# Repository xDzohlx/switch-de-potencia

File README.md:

# switch-de-potencia
Switch de alta corriente para encender baterías para suministrar potencia para un robot de combate para 180 amp 35V

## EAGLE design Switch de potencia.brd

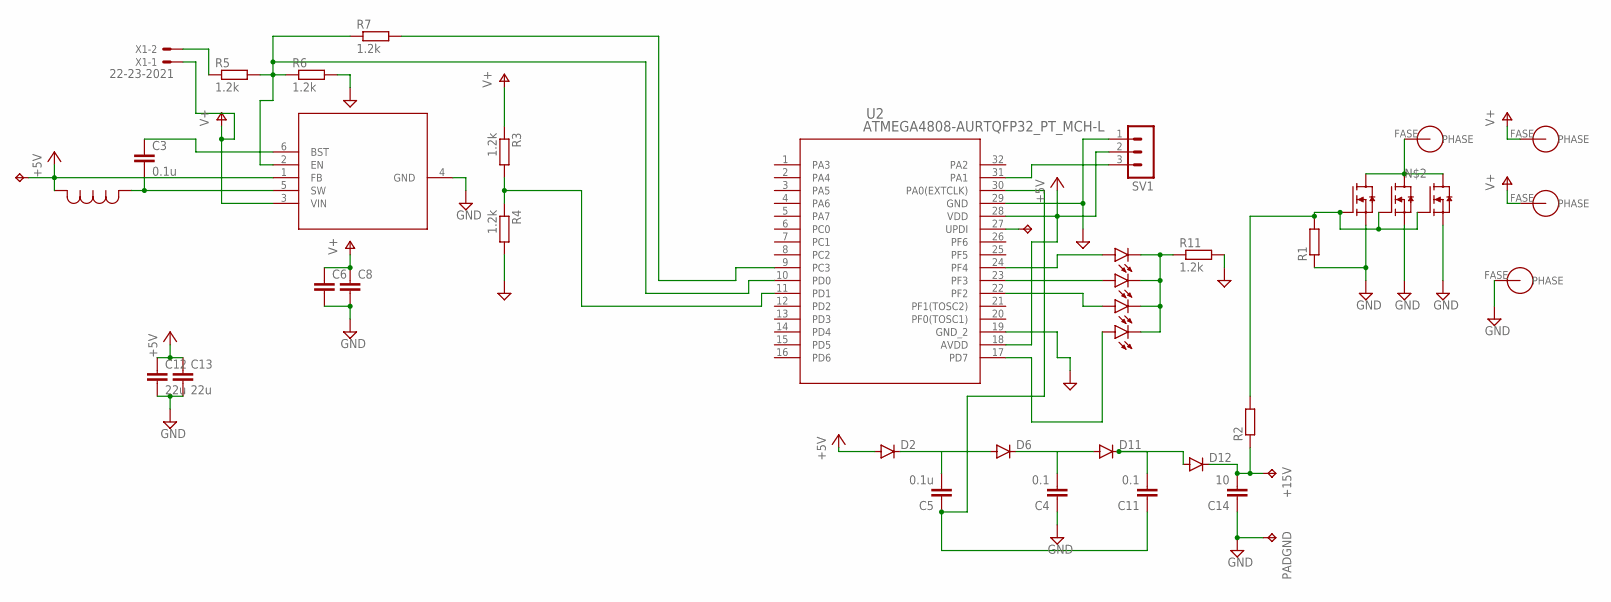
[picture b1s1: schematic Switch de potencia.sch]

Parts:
+15V: TPB1,27; B1,27
C3: 0.1u; C0402
C4, C11: 0.1; C0805
C5: 0.1u; C0805
C6, C8: C-EUC0805; C0805
C12, C13: 22u; C0402
C14: 10; C0805
D2, D6, D11, D12: DIODE-MINIMELF; MINIMELF
GND: PHASE; POWEROUT
LA1, LA2, LA3: IPB180N06S4-H1; PG-TO263-7-3
OUTPUT: PHASE; POWEROUT
PADGND: TPB1,27; B1,27
POWERON2, POWERON3, POWERON4, POWERON5: LEDCHIPLED_0603; CHIPLED_0603
R1, R2: R-EU_R0603; R0603
R3, R4, R5, R6, R7, R11: 1.2k; M0805
SV1: MA03-1
TP1, TP9: TPB1,27; B1,27
U2: ATMEGA4808-AURTQFP32_PT_MCH-L; TQFP32_PT_MCH-L
U3: AP63205WU-7SOIC_05WU-7_DIO-M; SOIC_05WU-7_DIO-M
U$1: INDUCTOR4.7; IND_NRS5030T100MMGJ_TAY
V+, V+1: PHASE; POWEROUT
X1: 22-23-2021

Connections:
+5V: C12.1, C13.1, D2.A, SV1.2, TP9.TP, U2.18 (AVDD), U2.28 (VDD), U3.1 (FB), U$1.1
GND: C4.1, C6.2, C8.2, C12.2, C13.2, C14.1, GND.FASE, LA1.2 (S), LA1.3 (S), LA1.5 (S), LA1.6 (S), LA1.7 (S), LA2.2 (S), LA2.3 (S), LA2.5 (S), LA2.6 (S), LA2.7 (S), LA3.2 (S), LA3.3 (S), LA3.5 (S), LA3.6 (S), LA3.7 (S), PADGND.TP, R1.1, R4.2, R6.2, R11.2, SV1.1, U2.19 (GND_2), U2.29 (GND), U3.4 (GND)
unnamed: LA1.1 (G), LA2.1 (G), LA3.1 (G), R1.2, R2.2
unnamed: LA1.8 (D), LA2.8 (D), LA3.8 (D), OUTPUT.FASE
unnamed: TP1.TP, U2.27 (UPDI)
unnamed: POWERON3.A, U2.24 (PF4)
unnamed: POWERON2.A, U2.23 (PF3)
unnamed: POWERON5.A, U2.22 (PF2)
unnamed: +15V.TP, C14.2, D12.C, R2.1
unnamed: C5.2, D2.C, D6.A
unnamed: R5.1, X1.2
unnamed: R3.2, R4.1, U2.11 (PD1)
unnamed: POWERON4.A, U2.17 (PD7)
unnamed: SV1.3, U2.31 (PA1)
unnamed: POWERON2.C, POWERON3.C, POWERON4.C, POWERON5.C, R11.1
unnamed: C3.2, U3.5 (SW), U$1.2
unnamed: R5.2, R6.1, R7.1, U2.10 (PD0), U3.2 (EN)
unnamed: R7.2, U2.9 (PC3)
unnamed: C5.1, C11.1, U2.30 (PA0(EXTCLK))
unnamed: C3.1, U3.6 (BST)
unnamed: C4.2, D6.C, D11.A
unnamed: C11.2, D11.C, D12.A
V+: C6.1, C8.1, R3.1, U3.3 (VIN), V+.FASE, V+1.FASE, X1.1

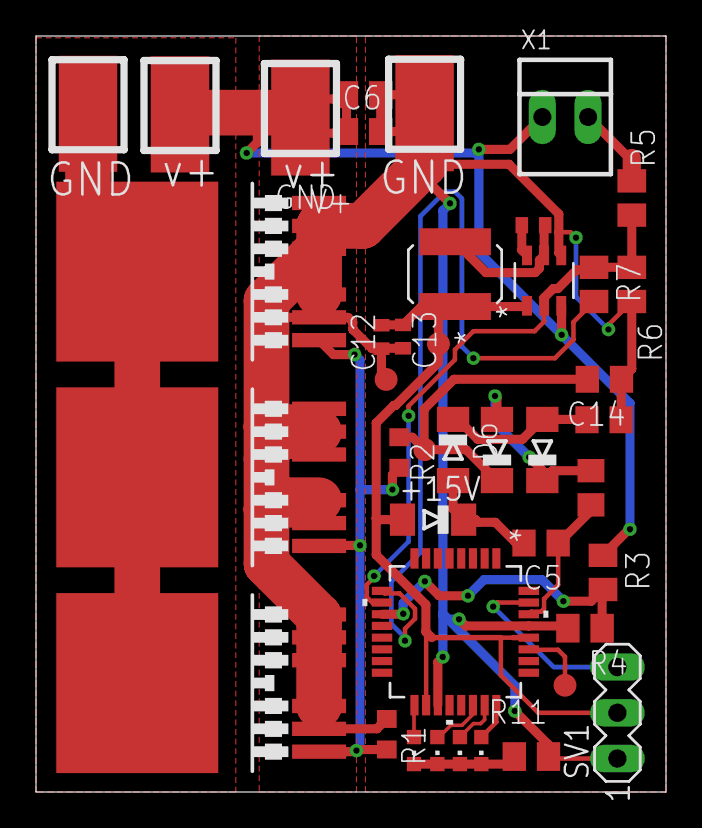
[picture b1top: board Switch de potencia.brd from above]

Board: 2 copper layers, 35.0 x 42.0 mm, 41 parts (0 on the bottom side), 23 nets.

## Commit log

2021-02-15 Add files via upload
    v1
2021-02-17 Create pcb
2021-02-21 Add files via upload
    Agregue usart , un pin para recibir datos

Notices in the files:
parts and their libraries:
COPYRIGHT: Copyright (C) 2018 Accelerated Designs. All rights reserved
